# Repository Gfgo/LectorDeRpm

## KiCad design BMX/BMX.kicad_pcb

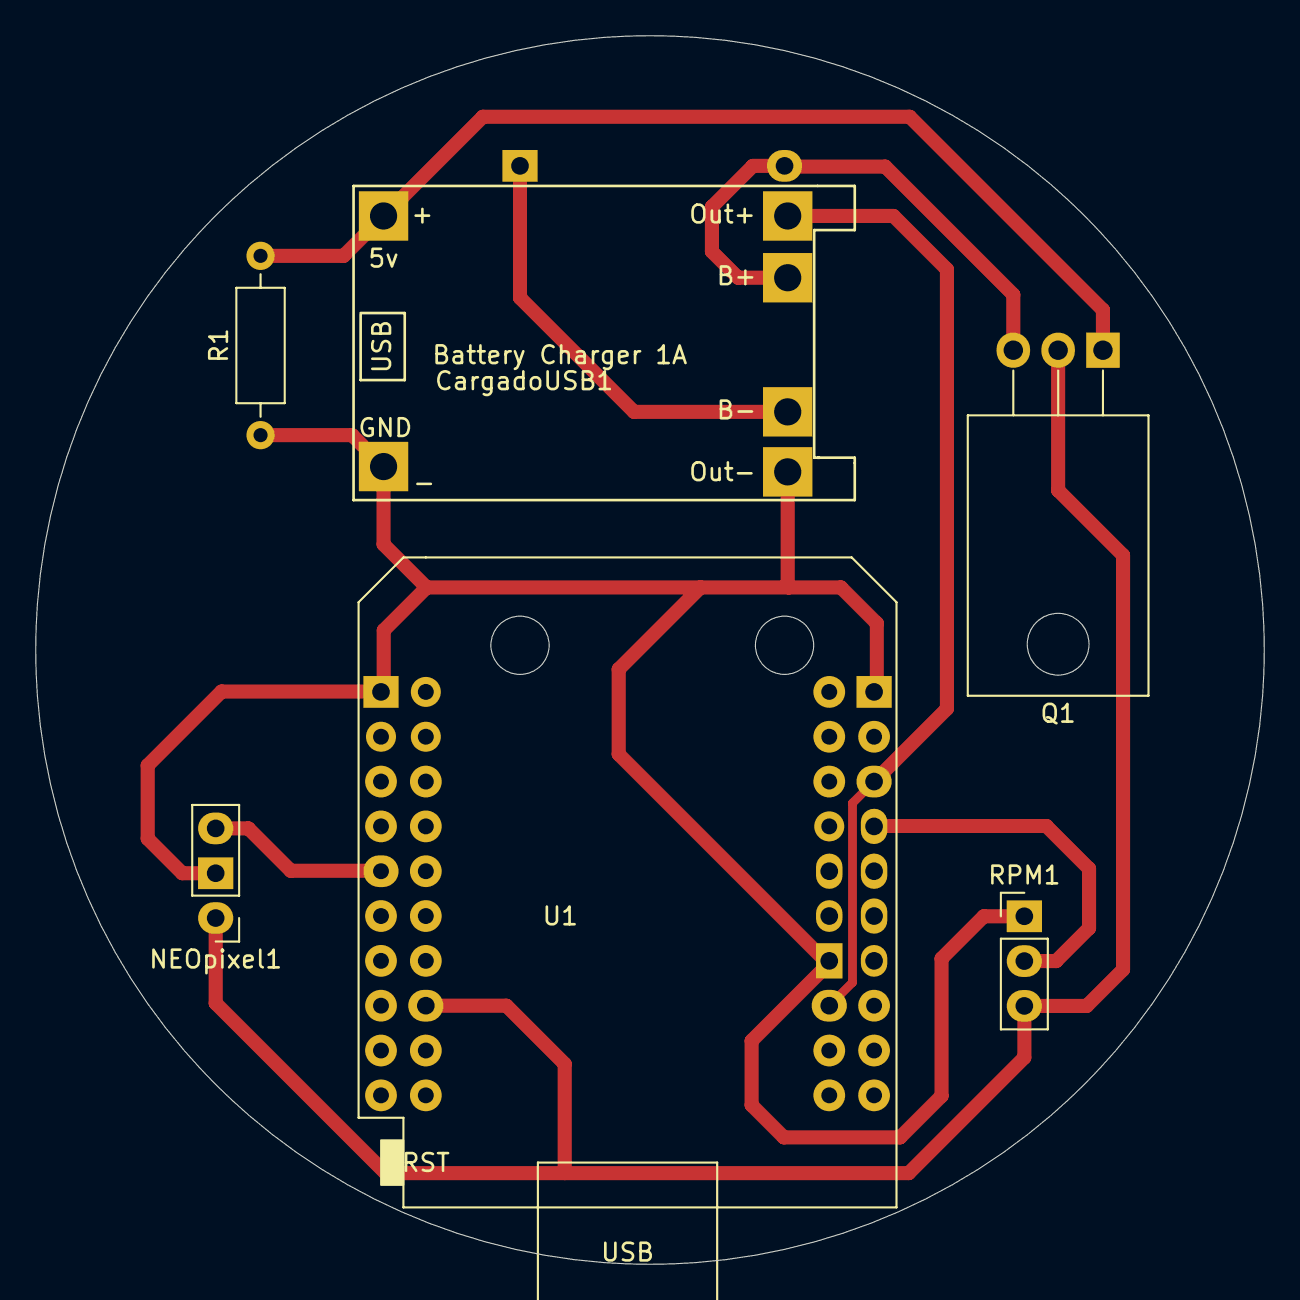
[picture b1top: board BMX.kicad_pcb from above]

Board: 2 copper layers, 69.6 x 69.6 mm, 7 parts (1 on the bottom side), 8 nets.

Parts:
Bateria3v1: Conn_01x02; BatteryHolder_Keystone_2462_2xAA
CargadoUSB1: Conn_01x06; TP4056-18650
NEOpixel1: Conn_01x03; PinHeader_1x03_P2.54mm_Vertical
Q1: IRF9540N; TO-220-3_Horizontal_TabDown
R1: 100k; R_Axial_DIN0207_L6.3mm_D2.5mm_P10.16mm_Horizontal
RPM1: Conn_01x03; PinHeader_1x03_P2.54mm_Vertical
U1: mini_esp32; ESP32_mini

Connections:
/IN: RPM1.2, U1.28
GND: CargadoUSB1.2, CargadoUSB1.4, NEOpixel1.2, R1.1, RPM1.1, U1.1, U1.22, U1.33
unnamed: Bateria3v1.1, CargadoUSB1.6
unnamed: Bateria3v1.2, CargadoUSB1.5, Q1.3
unnamed: CargadoUSB1.1, Q1.1
unnamed: CargadoUSB1.3, U1.26, U1.35
unnamed: NEOpixel1.1, Q1.2, RPM1.3, U1.16
unnamed: NEOpixel1.3, U1.9

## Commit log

2021-09-28 Create Contador_RPM.ino
    Programa de contador
2021-09-30 Rpm de Esp con problemas
2021-10-02 rpm222 lee rpm, no mapea falta bluetooth
2021-10-04 Create BLE.ino
    Comunicación BLE se necesita mensaje de bienvenida, identificación de conectado y envió de datos.
2021-10-07 Update BLE.ino
    Comunicacion bluetooth muetra datos en ble pero no los recibe
2021-10-07 Update BLE.ino
    BLE+RPM funcional solo lo hace por 10 sg
2021-10-08 Update BLE.ino
    falta controlar el tiempo de medición
2021-10-08 Update BLE.ino
    Falta conversión a Km/H
2021-10-09 Update BLE.ino
    TERMINADO conexion bluethoot y envio de Km/h
2021-10-09 TERMINADO
    solo se agregaron comentarios.
2021-10-26 Update BLE.ino
    Cambio menor comentario en nombre dispostivo
2021-12-14 Le RPM envia por ble falta que haga mas de 9 segundos
2021-12-14 Todo Ok
2022-05-19 Update BLE.ino
    Funcionando
2022-06-30 Versión funcional.
    Ultima versión con software y circuito funcional.
2022-08-10 Update BLE.ino
    Borrado de basura y organización de comentarios.
2023-07-14 Actualizacion
